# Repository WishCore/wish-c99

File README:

Quick build instructions

Build using cmake:

mkdir build
cd build 
cmake ..
make

Build using make (deprecated):

$ make -f make-linux.mk

Cross-compile build for ESP8266

Wish/Mist C implementation for esp8266

This is the repository for the proof-of-concept ANSI C implementation of
the Wish/Mist IoT communications stack.

This software targets the Olimex ESP8266-EVB hardware. It is a
nearly-fully functional Wish/Mist node, offering Wish "chat" service and a
Mist node making it possible to toggle the on-board relay on and off.

The Mist service includes a reply to the "control.model" command, as
well as "control.follow" and "control.write". Any writes targetting the
"relay" endpoint feature will be replied by a "follow" reply indicating
the new state.  Note however, that currently all the Mist service messages have
hard-coded source and destination WSIDs! For this reason, it will only
work with traditional Mist-UI.

The Mist command "control.map" is not supported.

The chat service replies to any messages by telling how much it has has
free space on the TCP receive ring buffer and heap, but sometimes it
will enter a period where a cryptic movie quote from "Le charme discret
de la bourgeoisie", by Louis Buñuel (1972) is output... You should try it!

Actually, this C implementation should be applicable to all MCUs, but it
is developed on the ESP8266 hardware.

The project was started using the SDK version 1.4.1
(esp_iot_sdk_v1.4.1_pre5_15_10_27.zip).

The project includes the mbedTLS 2.x library (under Apache 2.0 license).

This software uses the ESP8266 wifi stack in "station" mode - it will
connect to the network defined in the begining of user/user_main.c

The user should also note, that the IP address of the remote wish-core
is hardcoded (in user/user_main.c), and also that the local and remote
Wish user identity hashes are also hard-coded (in the begining of
wish/wish_io.c). The implemenatation currently only supports one Wish
connection. No "incoming" Wish connections are accepted by this node.

Overall, this software shows that Wish/Mist can clearly be implemeted on
microcontroller platforms offering just some 30 kilobytes of RAM
and ca. 250 kB Flash memory.

About the flash configuration of ESP8266 modules
This project targets modules with 2Mbyte (16Mbit) flash chips. 
Configuration of flash chip must be reflected in at least the following
places:

-The LD script, where the length of the irom0 segment must be correct
(however it should must be inside the first 1024 Kbytes)

-in Makefile, in the esptool.py elf2image step, you should provide
--flash_size and --flash_mode correctly
(See flash chip's datasheet for supportted SPI modes (dual, quad..)

-in Makefile, the esptool.py write_flash step MUST have the correct
flash_size and flash_mode defined.

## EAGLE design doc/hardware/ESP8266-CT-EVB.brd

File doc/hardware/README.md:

The MISTESP 2015 board
----

This file describes the evaluation and test board named MISTESP 2015.

The board was initially named ESP8266-CT-EVB, hence the name. The board
is designed using Eagle. The design rule checks have been slightly
modified so that they match those requreid by Prinel.

The Gerber files which were sent to Prinel for menufacturing are in the file mist-esp-manufacture-20151218.zip. Please see the file README.txt for information about the CAM job names used to create the Gerber files.

Possible hardware configurations
----

See the circuit diagram ESP8266-CT-EVB.pdf.

Powering options

* +12VDC, which is stepped down to ca. 3.2 V with LM317 regulator
* For battery powered applications, the board can be  alternatively powered with, 3.6V Lithium AA sized (non-rechargable) battery, such as the EVE ER14505

Serial communications options

* RS485 transciever, with its associated +5V supply from 7805 regulator. Note that the UART pins must be jumped together with the lines to/from the RS485 transciever.
* RS485 termination can be controlled
* The UART pins of ESP82 are directly accessible

The following configurations are mutually excelusive:

* I2C bus master, or
* One-wire bus master, which doubles as
* DHT-11 RH/temperature sensor interface, as the hardware is actually the same as for one-wire.

Other features

* LED indicator
* Three push buttons: Reset, Flashing mode enable 
* Two S0 pulse inputs

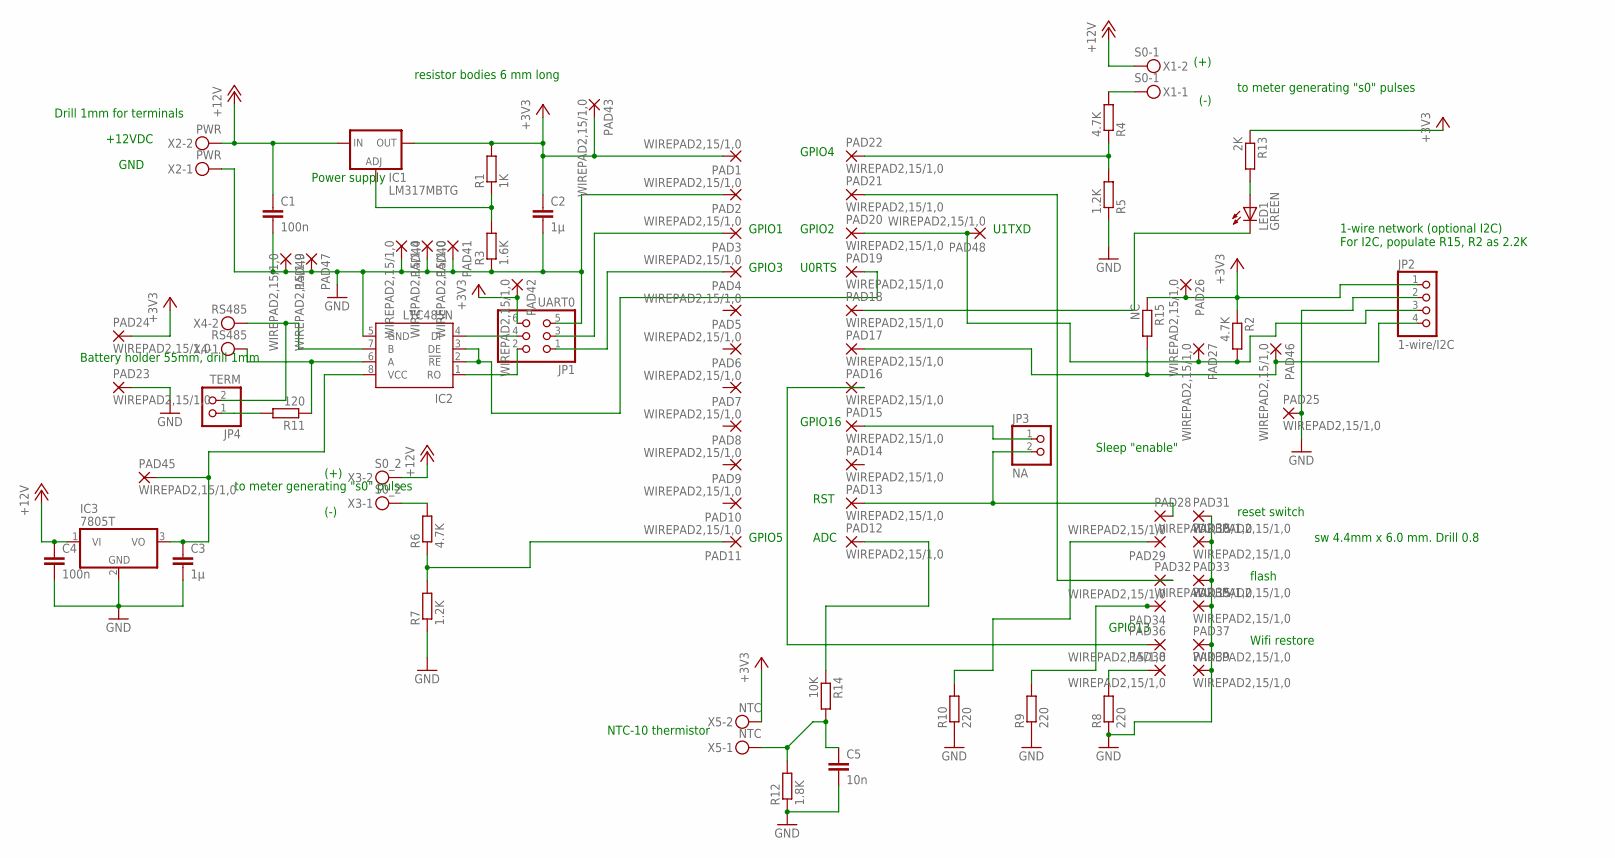
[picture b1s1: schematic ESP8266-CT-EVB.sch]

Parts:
C1, C4: 100n; C050-024X044
C2, C3: 1µ; C050-024X044
C5: 10n; C050-024X044
IC1: LM317MBTG; TO220L1
IC2: LTC485N; DIL08
IC3: 7805T; TO220H
JP1: UART0; 2X03
JP2: 1-wire/I2C; 1X04
JP3: NA; 1X02
JP4: TERM; 1X02
LED1: GREEN; LED3MM
PAD1, PAD2, PAD3, PAD4, PAD5, PAD6, PAD7, PAD8, PAD9, PAD10, PAD11, PAD12, PAD13, PAD14, PAD15, PAD16, PAD17, PAD18, PAD19, PAD20, PAD21, PAD22, PAD23, PAD24, PAD25, PAD26, PAD27, PAD28, PAD29, PAD30, PAD31, PAD32, PAD33, PAD34, PAD35, PAD36, PAD37, PAD38, PAD39, PAD40, PAD41, PAD42, PAD43, PAD44, PAD45, PAD46, PAD47, PAD48, PAD49: WIREPAD2,15/1,0; 2,15/1,0
R1: 1K; 0207/10
R2: 4.7K; 0207/2V
R3: 1.6K; 0207/10
R4, R6: 4.7K; 0207/10
R5, R7: 1.2K; 0207/10
R8, R9, R10: 220; 0207/2V
R11: 120; 0207/2V
R12: 1.8K; 0207/10
R13: 2K; 0207/7
R14: 10K; 0207/2V
R15: NC; 0207/2V
X1: S0-1; MKDSN1,5/2-5,08
X2: PWR; MKDSN1,5/2-5,08
X3: S0_2; MKDSN1,5/2-5,08
X4: RS485; MKDSN1,5/2-5,08
X5: NTC; MKDSN1,5/2-5,08

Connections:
+3V3: C2.1, IC1.2 (OUT), JP1.6, JP2.1, PAD1.1, PAD24.1, PAD26.1, PAD42.1, PAD43.1, R1.2, R2.1, R13.1, R15.1, X5.2
+12V: C1.1, C4.1, IC1.3 (IN), IC3.1 (VI), X1.2, X2.2, X3.2
DQ: JP2.3, PAD20.1, PAD27.1, PAD48.1, R2.2
GND: C1.2, C2.2, C3.2, C4.2, C5.2, IC2.5 (GND), IC3.2 (GND), JP1.5, JP2.2, PAD2.1, PAD23.1, PAD25.1, PAD30.1, PAD31.1, PAD33.1, PAD35.1, PAD37.1, PAD39.1, PAD40.1, PAD41.1, PAD44.1, PAD47.1, PAD49.1, R3.1, R5.1, R7.1, R8.1, R9.1, R10.1, R12.1, X2.1
unnamed: R6.2, X3.1
unnamed: R4.2, X1.1
unnamed: IC1.1 (ADJ), R1.1, R3.2
unnamed: PAD11.1, R6.1, R7.2
unnamed: PAD38.1, R8.2
unnamed: PAD22.1, R4.1, R5.2
unnamed: LED1.A, R13.2
unnamed: PAD21.1, PAD32.1
unnamed: JP3.2, PAD13.1, PAD28.1
unnamed: LED1.K (C), PAD18.1
unnamed: JP2.4, PAD17.1, PAD46.1, R15.2
unnamed: JP3.1, PAD15.1
unnamed: PAD34.1, R9.2
unnamed: PAD29.1, R10.2
unnamed: C3.1, IC2.8 (VCC), IC3.3 (VO), PAD45.1
unnamed: IC2.7 (B), JP4.2, X4.2
unnamed: IC2.6 (A), R11.1, X4.1
unnamed: JP4.1, R11.2
unnamed: JP1.3, PAD3.1
unnamed: JP1.1, PAD4.1
unnamed: PAD12.1, R14.1
unnamed: IC2.2 (!RE), IC2.3 (DE), PAD19.1
unnamed: C5.1, R12.2, R14.2, X5.1
unnamed: PAD16.1, PAD36.1
unnamed: IC2.1 (RO), JP1.2
unnamed: IC2.4 (DI), JP1.4

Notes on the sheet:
+12VDC
GND
1-wire network (optional I2C) For I2C, populate R15, R2 as 2.2K
GPIO13
GPIO2
GPIO3
GPIO1
RST
GPIO16
to meter generating "s0" pulses
(+)
(-)
GPIO5
Power supply
Sleep "enable"
Battery holder 55mm, drill 1mm
GPIO4
reset switch
flash
Wifi restore
U0RTS
ADC
U1TXD
sw 4.4mm x 6.0 mm. Drill 0.8
Drill 1mm for terminals
resistor bodies 6 mm long
NTC-10 thermistor

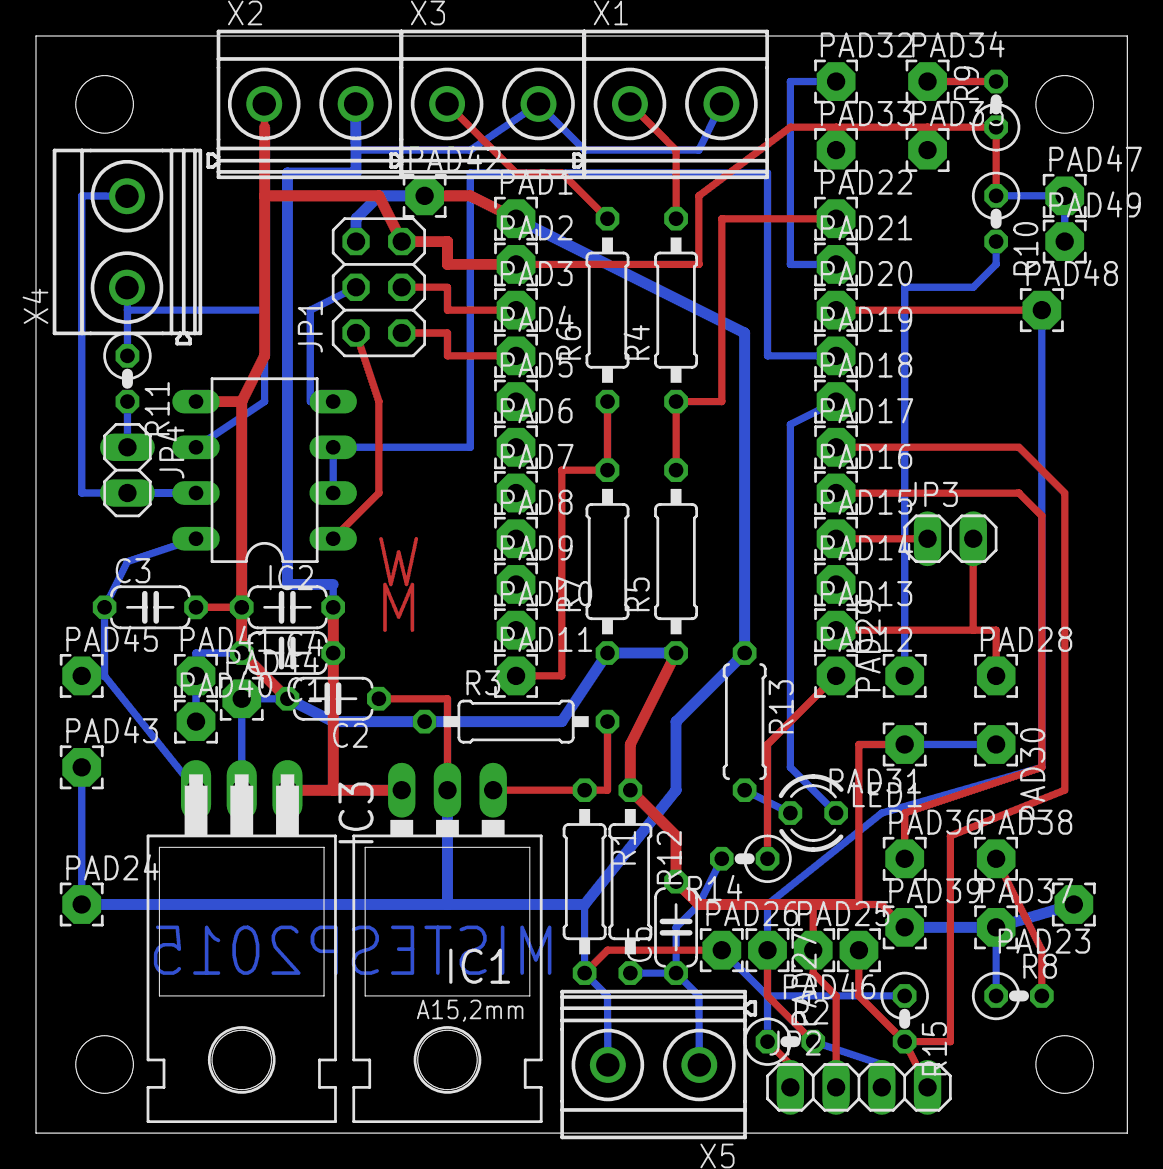
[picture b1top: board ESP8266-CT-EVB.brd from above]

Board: 2 copper layers, 60.6 x 61.0 mm, 82 parts (0 on the bottom side), 30 nets.

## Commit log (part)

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2017-02-08 Working towards multiple core_client support.
2017-02-15 Change to core RPC identity.create or identity.remove
    When identity is created/removed, it becomes online for each local
    service on the core, and peer updates are sent to the services
    accordingly.
2017-02-15 Fixed online and offline signals which were disabled since mist-api refactoring.
2017-02-16 Wish core can now be compiled on its own. See this commit's changes for more in depth changes.
2017-02-16 Removed mist_c99 binary accidentally added.
2017-02-19 Fixed identity remove update_identities call with actual core instead of NULL.
2017-02-20 Refactored in bson_visit('title', bson_doc) format.
2017-02-20 Refactored wish_context (i.e. connections) store to be pointer in wish_core_t.
2017-02-21 Moved ldiscover db as pointer to wish_core_t.
2017-02-23 Init service registry from heap.
2017-02-24 Added friend request list, accept and core signal friendRequest.
2017-02-28 Refactored wish_context_t to wish_connection_t.
2017-03-01 Refactored wish_rpc_ctx to rpc_server_req. Updated to newest wish-rpc.
2017-03-02 Update to compile on OSX again.
2017-03-02 Fixed invalid emit_broadcast call.
2017-03-03 Refactored ctx to connection in wish_io.c
2017-03-03 Moved check connection liveliness to wish_connection_mgr. Added wish_connections_init with timer init.
2017-03-04 Added wish_app_entry pointer to req->context in wish_app_rpc_server. Minor cleanup.
2017-03-04 Minor cleanup and docs.
2017-03-04 wish_connections_connect_tcp no longer uses uid[0], but given luid param for uid. Minor cleanup.
2017-03-05 Moved host id to wish_config, and is now stored as 'id' in wish.conf.
2017-03-05 Connection attempt debug output changed.
2017-03-07 Refactored rctx to relay.
2017-03-07 Refactored wish_core_t.relay_ctx to wish_core_t.relay_db.
2017-03-07 Deprecated write_bson_error, replaced by calls to wish_rpc_server_error
    Added returns after calls to wish_rpc_server_error where missing
2017-03-07 Fixed local discovery initialization problem with ghost entries.
2017-03-10 Fixed ready signal frame length bug. Updated wish_rpc.
2017-03-10 Added localDiscovery signal on new or dropped local discovery entry. Added wld.announce for manually sending advertisements.
2017-03-10 Refactor wish_connections members: local_wuid, remote_wuid, remote_hostid and rmt_ip_addr, rctx to luid, ruid, rhid, remote_ip_addr and relay respectively.
2017-03-11 Fixed argument checks for acl.addUserRole.
2017-03-13 Some additional debug output and bson object rewritten in peers_callback.
2017-03-13 Moved implemetation of wish_relay_get_contexts to common wish code
2017-03-13 Added file remove because lseek is broken on Android.
2017-03-14 Enure exceptfds is initialized: FD_ZERO(&exceptfds);.
2017-03-14 Change in wish_core_app_rpc_cleanup_requests
    When a service is removed from the core's service registry, the
    outstanding RPC requests are cleaned up by comparing context pointers,
    instead of comparing "local_wsid"
2017-03-15 identity.export binary reverted, but added signed alternative for new format.
2017-03-15 Added transports to handshake message, and partial parsing.
2017-03-15 Minor cleanup and refactor in wish_core_feed_to_rpc_server.
2017-03-16 Test release cycle.
2017-03-21 Fixed MSG_NOSIGNAL vs SO_NOSIGPIPE incompatibility with OSX, and disbaled find_local_default_route implementation on OSX.
2017-04-24 Added EPERM check to wish_send_advertizement.
2017-04-25 Protocol change in friendRequest
    The friend request connection is now encrypted with AES using a key
    determined with the DHM key exchange scheme.
    The friend request connection handshake now looks like a normal
    connection, only the connection type in the preable still indicates it
    is a friend req connection. The connection setup goes through the same
    DHM key exchange steps as in the case of a normal connection. Signatures
2017-04-26 Removed #if 0'ed code
2017-04-26 Continued implementation of "new-style" friend requests
    The friend requests do not currently work, as the accepting (or
    declining) a friend request does not work. Friend requests however end
    up the fiend request list correctly.
2017-05-03 Re-enabled friend requests.
    The friend request now works using a normal which connection, which is
    flagged as insecure by means on ctx->friend_request_connection==true.
    The friend request is sent as core-to-core RPC message, and if the
    request is accepted, the recepient's own certificate is sent back to the
    requestor. In case of fried req declined, an RPC message with
    appropriate message is sent.
2017-05-10 Amending: Fixed uninitialized claim in identity.sign.
2017-05-11 Cleaned up the app_rpc identity.export to use the wish_identity implementation.
2017-05-11 Started parsing signatures from new format for identity_verify.
2017-05-12 Added identity.friendRequest(uid, cert) compatible with directory.find().
2017-06-08 Enlarged the wish-app tcp receive buffer from 1024 bytes to 64KiB. Added error output if frame is larger than buffer.
2017-06-21 Simplified identity_get implementation. Added support for showing transports in identity.get.
2017-07-20 Mejor refactoring for 0.8.0 and some incompatibilities
    This commit will require significant testing!
    * refactored out cbson in favor of bson
    (re-wrote all usages of cbson to bson)
    * All wish-rpc handler now have args a const uint8_t*
    * peers messages between cores are simplified
2017-07-21 Fixed bson iterator reinit.
2017-07-26 Moved to using new simplified rpc api.
2017-07-27 Initial documentation using sphinx.
2017-07-27 Renamed wish directory to src.
2017-07-27 Moved connetcions api implementation to own file.
2017-07-27 Moved local discovery api implementation to own file.
2017-07-27 Use core rpc_client instead of static core2remote.
2017-07-28 Fixed doxygen.
2017-08-05 Fix saving transports in friend requests
    Transports that are listed in the 'meta' element of friend request are
    now saved to the internal identity/contact representation, both on the
    friend requestor and requestee side.
2017-08-10 Fixing issue which friend requests list add
    The bug caused UIDs with 0x00 bytes to be only partially copied
    (strncpy vs. memcpy!)
2017-08-14 Fixed inverted bool output for bson_visit.
2017-08-14 Fixed unfinished bson bug when sending frames from core to app.
2017-08-16 Updated README for cmake build.
2017-08-21 Started implementing core rpc commands with acl, for remote administration etc.
2017-08-22 Got BSON copy append into working.
2017-08-24 Added identity.list, export and sign to remotely executable commands.
2017-08-24 Added return for bson_copy_with_state BSON_SIZE_OVERFLOW.
2017-08-24 Disabled test building, due to problems with Android build script.
2017-08-25 Added reading signed meta from friendRequest, and increased max data size to 512 bytes.
2017-08-28 Fixed double data fields in identity sign response.
2017-08-28 Added primitive support for identity discovery via friend request meta data.
2017-08-30 Updated to new wish_rpc.
2017-08-30 Updated to newly refactored wish-rpc.
2017-08-31 Added identity.remove to remotely executable commands.
2017-09-13 Enlarged buffer for connections request.
2017-09-14 Added a bson_visit of the payload of services.send (but it is commented out)
    This was added to ease debuging later.
2017-09-18 Updated wish-rpc-c99.
2017-09-26 Refactoring wish_io.h is now wish_connection.h. Reduced debug output.
2017-09-30 Cleaned up some debug output, mainly around friend requests. Refactored new_ctx to connection in wish_relay_client.
2017-10-02 Include stdlib.h for strtol
2017-10-03 Deleted the esp8266 port from wish-c99
    The new place for the up-to-date port is wish-port-esp8266
2017-10-08 Added option to allocate buffers from heap (at compile time)
    This was needed specifically to enable receiving friendRequestAccept
    from a remote node
2017-10-17 Updated wish-rpc-c99 and removed excessive debug output.
2017-10-23 Updated wish-rpc, but it still needs work.
2017-10-24 assert.h inclusion guarded by macro, added the macro to unix port config
2017-10-27 Updated readme.
2017-10-27 CMAKE Probably not compatible changes, but they are commented out. Just for reference.
2017-11-03 Adorn with macro so that strtol is used on esp8266 and strtoimax on others
2017-11-13 Added wish event for requesting connection abort
2017-11-20 Redundant connections are checked for when connection is established
2017-12-04 The identity structure is initialised to 0 before the identity is created
2017-12-04 wld functions can be disabled with cmd line options -l and -b
2017-12-05 Added WLD_META_PRODUCT for exposing a hint about a core being discovered via wld.
2017-12-05 Support multiple transports
    * identity.create will add all the relay servers configured as
    transports to identity
    * transports are saved to and restored from the id db
    * multiple transports are added to identity.get and identity.export
2017-12-07 Fix comment
2017-12-11 Added identity.update to connections.request.
2017-12-14 Updated identity.update to take any type of meta arguments. Added identity.get to remotely accessible commands.
2017-12-15 Typo.
2017-12-16 Fixed double free problem in identity.update and permissions.
2017-12-16 Added functions wish_identity_meta and wish_identity_permissions for reading.
2017-12-19 Added corresponding wish_identity_destroy to identity load
2017-12-19 Added alias update for wld with same ruid, rhid.
2017-12-21 Added bson_replace_element. Added ensure_space to bson_copy_with_state. Added working, but crappy, identity.update implementation.
2017-12-21 Updated identity.permissions to use new bson_update function.
2017-12-26 Fixing memory leak in identity.permissions handler
2017-12-27 Added build scripts in tools folder. Added conditional ia32 build option.
2017-12-27 Added x64 and ia32 to stripped targets for releases.
2017-12-28 Updated wish-rpc-c99
2017-12-28 Changed and disabled appending of local ip addr as transports in connection handshake
2018-01-02 Fixing memory leaks
2018-01-04 Reverting change in commit f41f9981b related to wish_ldiscover_entry_from_bson()
2018-01-04 Added Apache-2.0 license text file. Move source release file instead of copying when done.
2018-01-07 strdup replaced with wish_platform_strdup
    If WITHOUT_STRDUP is defined, an alternative implementation is used.
    Else strdup will be directly called
2018-01-09 Fixed app sending zero length frame on app connection. App using services.send now receives error if no connection available.
2018-01-11 When looking up connections between identities, ignore connections that are friend request connections.
2018-01-11 Enabled "relay: true" in case the connection is incoming via relay
2018-01-12 Added connections.disconnectAll.
2018-01-24 Fix variable name if on big endian system
2018-01-26 Fixed memory leak when using services.send with local service.
2018-02-16 Linux port connection limit from 10 to 100.
2018-02-16 Added NULL check warning.
2018-02-22 Clean up output a bit
2018-02-26 Added error handling in case wish_connection_init returns null when opening a friend request connection.
2018-02-27 Change in wld: all hosts can now connect, independent of rhid
2018-03-18 Implemented core-to-core RPC server ACL check function
    The requests requiring elevated privileges require that the contact has
    permissions.core.owner: true
2018-03-19 Fixed bug: if core received friend request connection to an identity which did not exist, then the core crashed.
2018-03-21 Removed excessive (and faulty call) to relay_periodic
2018-03-27 Re-introducing WISH_REMOTE_MANAGEMENTS, which means that wish core2core RPC acl is disabled
2018-04-27 Added local discovery class option to CMakeLists.txt. (use ccmake)
2018-06-13 gitignore update
2018-08-02 Committing deletion of file
2018-08-02 .gitignore changed
2018-08-02 Removing ed25519 subrepo
2018-08-02 Removed mbedtls-2.1.2
2018-08-02 Removed uthash
2018-08-02 Removed libuv headers
2018-08-03 Added more info on how the repo was formed
2018-08-03 Deleted outdated TODO file.
2018-08-09 Removed faulty travis file.
2018-08-14 Applied Apache 2 license via LICENSE file.
2018-08-14 Update LICENSE
2020-11-07 Added peer name to peers listing.
